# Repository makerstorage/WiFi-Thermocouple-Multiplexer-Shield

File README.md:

**WiFi Thermocouple Multiplexer Shield**

For more details, check out the product page at

https://makerstorage.com/index.php?id_product=35&controller=product

MakerStorage invests time and resources providing this open source design, please support MakerStorage and open-source hardware by purchasing products from MakerStorage!

Designed by MakerStorage LLC.

Creative Commons Attribution, Share-Alike license, check https://creativecommons.org/licenses/by-sa/3.0/ for more information All text above must be included in any redistribution

This Shield is designed to easily allow multiple high-temperature readings with an ESP8266 control board. Screw terminals are provided for thermocouple connections.

* Multiplexing seven K-type thermocouples (Can read all sensors under a second)
* Wifi capability (example firmware for local server and Amazon AWS IoT)
* Suitable for only Lolin models of ESP8266 (27mm between headers)
* Onboard Max31855KASA  Cold-Junction Compensated Thermocouple-to-Digital Converter
* Works with K type thermocouples
-200°C to +1350°C output in 0.25 degree increments - note that K thermocouples have about ±2°C to ±6°C accuracy

**Areas to use:**

* Automotive  Engine, Exhaust and Brake temperatures

* Ovens, Furnaces, and Kilns

* Freezer or Cryogenic monitoring

* Chemical Processes

* IoT applications like Multi-Zone Temperature Monitoring, Data Acquisition or Logging Systems

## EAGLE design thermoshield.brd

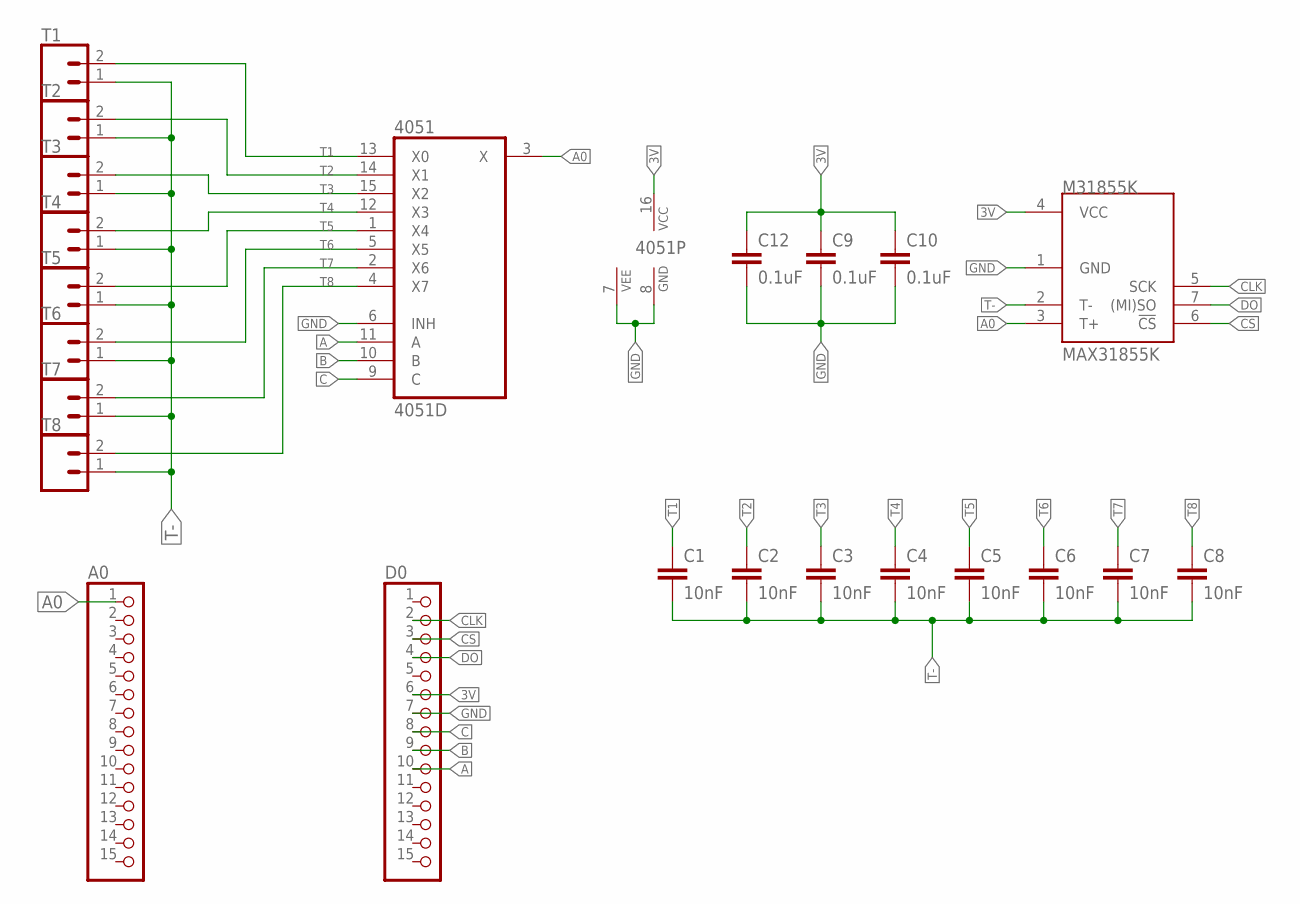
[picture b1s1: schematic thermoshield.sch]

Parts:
4051: 4051D; SO16
A0: PINHD-1X15; 1X15
C1, C2, C3, C4, C5, C6, C7, C8: 10nF; 0603
C9, C10, C12: 0.1uF; 0603
D0: PINHD-1X15; 1X15
M31855K: MAX31855K; SO08
T1, T2, T3, T4, T5, T6, T7, T8: CONN_023.5MM-NO_SILK; SCREWTERMINAL-3.5MM-2-NS

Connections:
3V: 4051.16 (VCC), C9.1, C10.1, C12.1, D0.6, M31855K.4 (VCC)
A: 4051.11 (A), D0.10
A0: 4051.3 (X), A0.1, M31855K.3 (T+)
B: 4051.10 (B), D0.9
C: 4051.9 (C), D0.8
CLK: D0.2, M31855K.5 (SCK)
CS: D0.3, M31855K.6 (!CS)
DO: D0.4, M31855K.7 ((MI)SO)
GND: 4051.6 (INH), 4051.7 (VEE), 4051.8 (GND), C9.2, C10.2, C12.2, D0.7, M31855K.1 (GND)
T1: 4051.13 (X0), C1.1, T1.2
T2: 4051.14 (X1), C2.1, T2.2
T3: 4051.15 (X2), C3.1, T3.2
T4: 4051.12 (X3), C4.1, T4.2
T5: 4051.1 (X4), C5.1, T5.2
T6: 4051.5 (X5), C6.1, T6.2
T7: 4051.2 (X6), C7.1, T7.2
T8: 4051.4 (X7), C8.1, T8.2
T-: C1.2, C2.2, C3.2, C4.2, C5.2, C6.2, C7.2, C8.2, M31855K.2 (T-), T1.1, T2.1, T3.1, T4.1, T5.1, T6.1, T7.1, T8.1

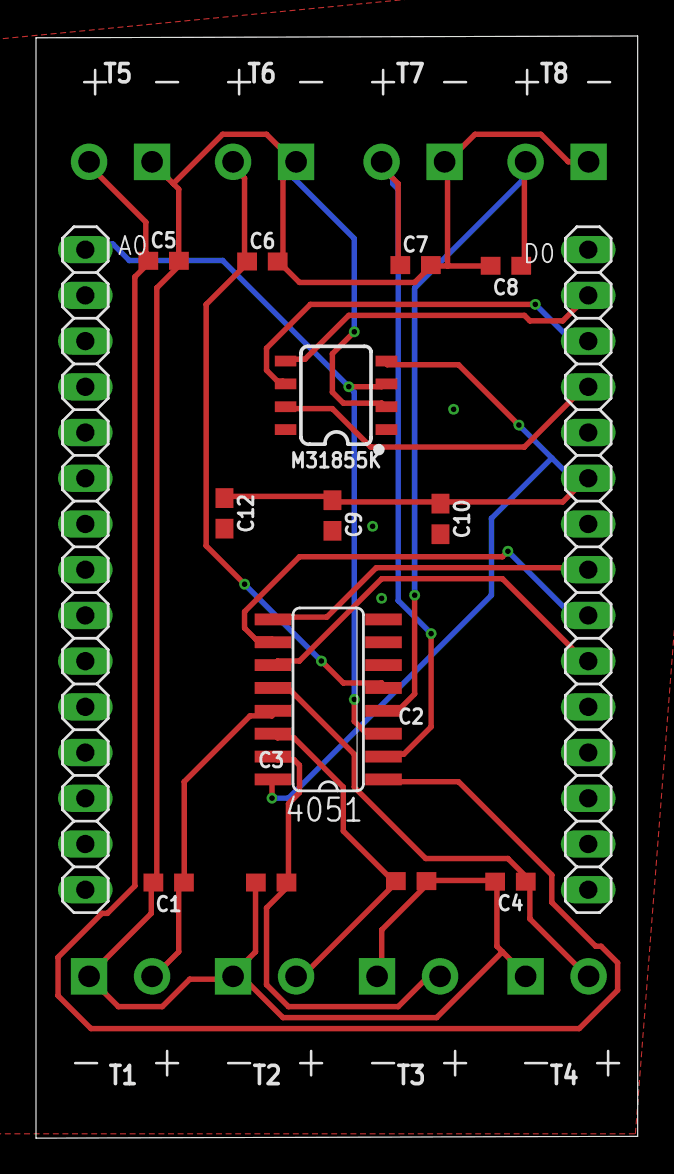
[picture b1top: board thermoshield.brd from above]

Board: 2 copper layers, 33.4 x 61.2 mm, 23 parts (0 on the bottom side), 18 nets.

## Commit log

2020-02-08 multi_thermo source files

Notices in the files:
parts and their libraries:
SparkFun-Capacitors: Licensing: Creative Commons ShareAlike 4.0 International - https://creativecommons.org/licenses/by-sa/4.0
